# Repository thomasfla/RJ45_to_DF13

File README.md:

# RJ45_to_DF13
Simple board to expose RJ45 pairs to 2pin DF13 connectors

* RJ45 : 1x 54602-908LF
* DF13 : 4x DF13-2P-1.25DSA(25)

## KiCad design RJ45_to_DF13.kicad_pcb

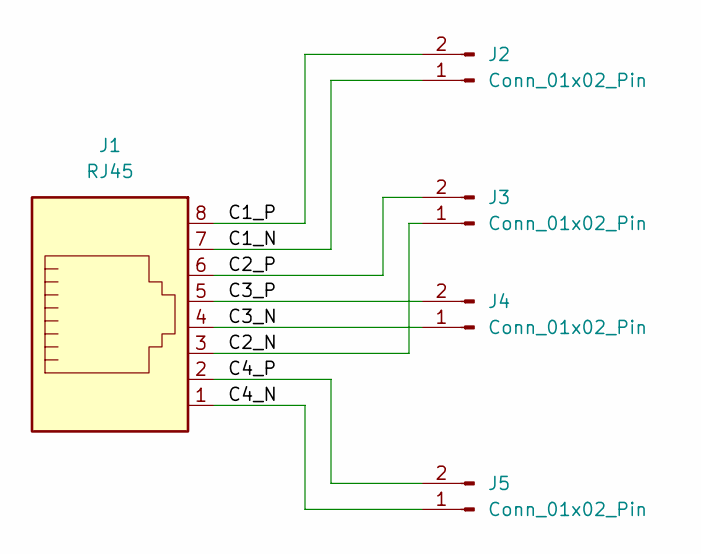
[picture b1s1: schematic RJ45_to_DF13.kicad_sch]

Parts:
J1: RJ45; RJ45_Amphenol_54602-x08_Horizontal
J2, J3, J4, J5: Conn_01x02_Pin; Hirose_DF13-02P-1.25DSA_1x02_P1.25mm_Vertical

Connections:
/C1_N: J1.7, J2.1
/C1_P: J1.8, J2.2
/C2_N: J1.3, J3.1
/C2_P: J1.6, J3.2
/C3_N: J1.4, J4.1
/C3_P: J1.5, J4.2
/C4_N: J1.1, J5.1
/C4_P: J1.2, J5.2

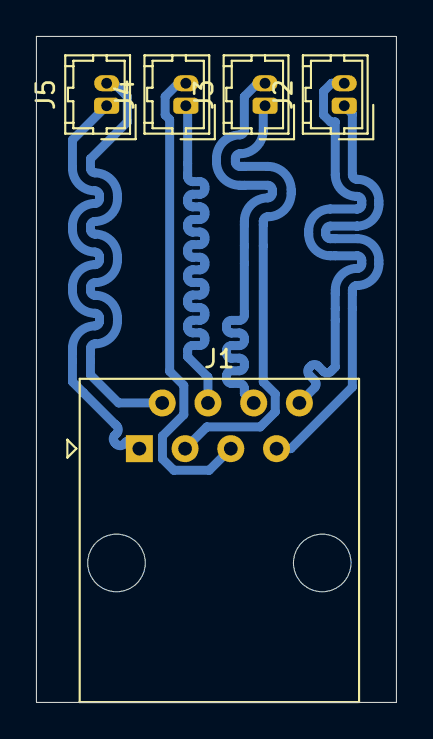
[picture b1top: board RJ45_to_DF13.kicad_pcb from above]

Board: 2 copper layers, 20.0 x 37.0 mm, 5 parts (0 on the bottom side), 8 nets.

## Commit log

2024-10-18 add files
2024-10-18 add bom in readme
